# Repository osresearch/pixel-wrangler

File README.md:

# Pixel Wrangler: HDMI to whatever

The Pixel Wrangler is a tool for converting HDMI video into anything else.
It uses an ice40up5k FPGA to decode the video stream and stores a section
of it in the block RAM, which can then be clocked out of the 16 GPIO pins
in any other format required.

Since the FPGA has total flexibility in how it drives the output pins
it is easily adaptable to different protocols.  Some examples that are possible:

* Classic CRT like the original Mac or Hercules monitors
* LED matrices
* Flip dots
* LED strips (ws2812 or other protocols)
* Lots of servos for "wooden mirrors"

## Does it work?

Mostly! The EDID output is good enough to convince Linux to use it as
a normal, if low-resolution, display.  The `mac.bin` monitor mode has
"*live dithering*" to convert the color display into 1-bit, which
works well enough to [play Doom on a 9" Mac Plus](https://www.youtube.com/watch?v=UI3e4YboR_g)!

With `xrandr` it is possible to
have it use a small section of the primary monitor if you don't want a
separate head:

```
xrandr --output HDMI-2 --pos 350x100
```

There are some [problems with the v0 boards](https://github.com/osresearch/pixel-wrangler/issues/22),
one of which reqiures a bodge wire on the i2c lines.  The 5v pullups on
the source side of the HDMI i2c also might cause problems in the FPGA,
so the boards need some redesign.

The [TMDS D1 and D2 channels aren't working](https://github.com/osresearch/pixel-wrangler/issues/23),
so right now only the blue data on channel D0 is used.
This might be a clock phase issue or it might be a larger problem;
more research is needed.

The USB Micro is directly connected to the ice40up5k and the flash
can be loaded with [TinyFPGA bootloader `pixelwrangler` branch](https://github.com/osresearch/TinyFPGA-Bootloader/tree/pixelwrangler)
to allow new bit streams to be uploaded into the device.
The [`multiboot.bin`](image/multiboot.bin) is prebuilt and can
be flashed with your SPI flasher of choice and then the `bootmeta.json`
and `boardmeta.json` can be written into the flash security pages.

## PCB design

[v0 Schematic](pcb/wrangler_v0.pdf) is based on the [UPduino v3.0 by tinyvision.ai](https://www.tindie.com/products/tinyvision_ai/upduino-v31-low-cost-lattice-ice40-fpga-board/),
heavily modified for this specific application.

The HDMI connector has one differential pair carrying a 25 MHz clock and three differential
pairs running at 250 MHz and carrying 10 bits per pixel.  The clock *must* connect
to the one pin on the ice40up5k that has a LVDS connection to the global clock buffer
so that the pixel clock can be quickly fanned-out to the rest of the logic that uses it.
The three data pairs are routed to the LVDS inputs; D0 and D1 are inverted so that they
don't have to cross on the PCB and must be flipped in the logic.

## Limitations

* Only "baseline video" is supported
  * 640x480 @ 60Hz
  * 25 MHz maximum pixel clock
* 1 Mib frame buffer memory in the ice40. Resolutions supported are:
  * 1024x1024x1
  * 512x512x4
  * 256x256x16
  * 256x128x24
* 3.3V IO on GPIO pins
* No protection against shorts or overcurrent. Be careful!
* Boot loader requires button press to reset
* There isn't any USB support in the bit stream tree yet.

## Dithering

Dithering uses Ordered Blue Noise Dithering. Pattern is from [gao-duan](https://github.com/gao-duan/BlueNoise) (MIT Licensed).
Currently limited to a 64x64 size pattern; ideally a larger RGB
image could be loaded from the SPI flash at boot time, which would
allow three channel dithering without repeating across the screen.

## Todo

* [X] Finish board design -- ordered!
* [X] EDID ROM and i2c interface
* [X] DDR on input for ~~high-res~~ inputs
* [X] Classic Mac mode -- working!
* [ ] Fix TMDS channel D1 and D2 decoding
* [ ] Documentation on writing new interfaces
* [ ] LED strip mode
* [ ] Load larger dithering pattern from flash?

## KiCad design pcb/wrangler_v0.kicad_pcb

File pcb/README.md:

This is derived from the UPduino v3 board design by tinyvision-ai-inc:
https://github.com/tinyvision-ai-inc/UPduino-v3.0

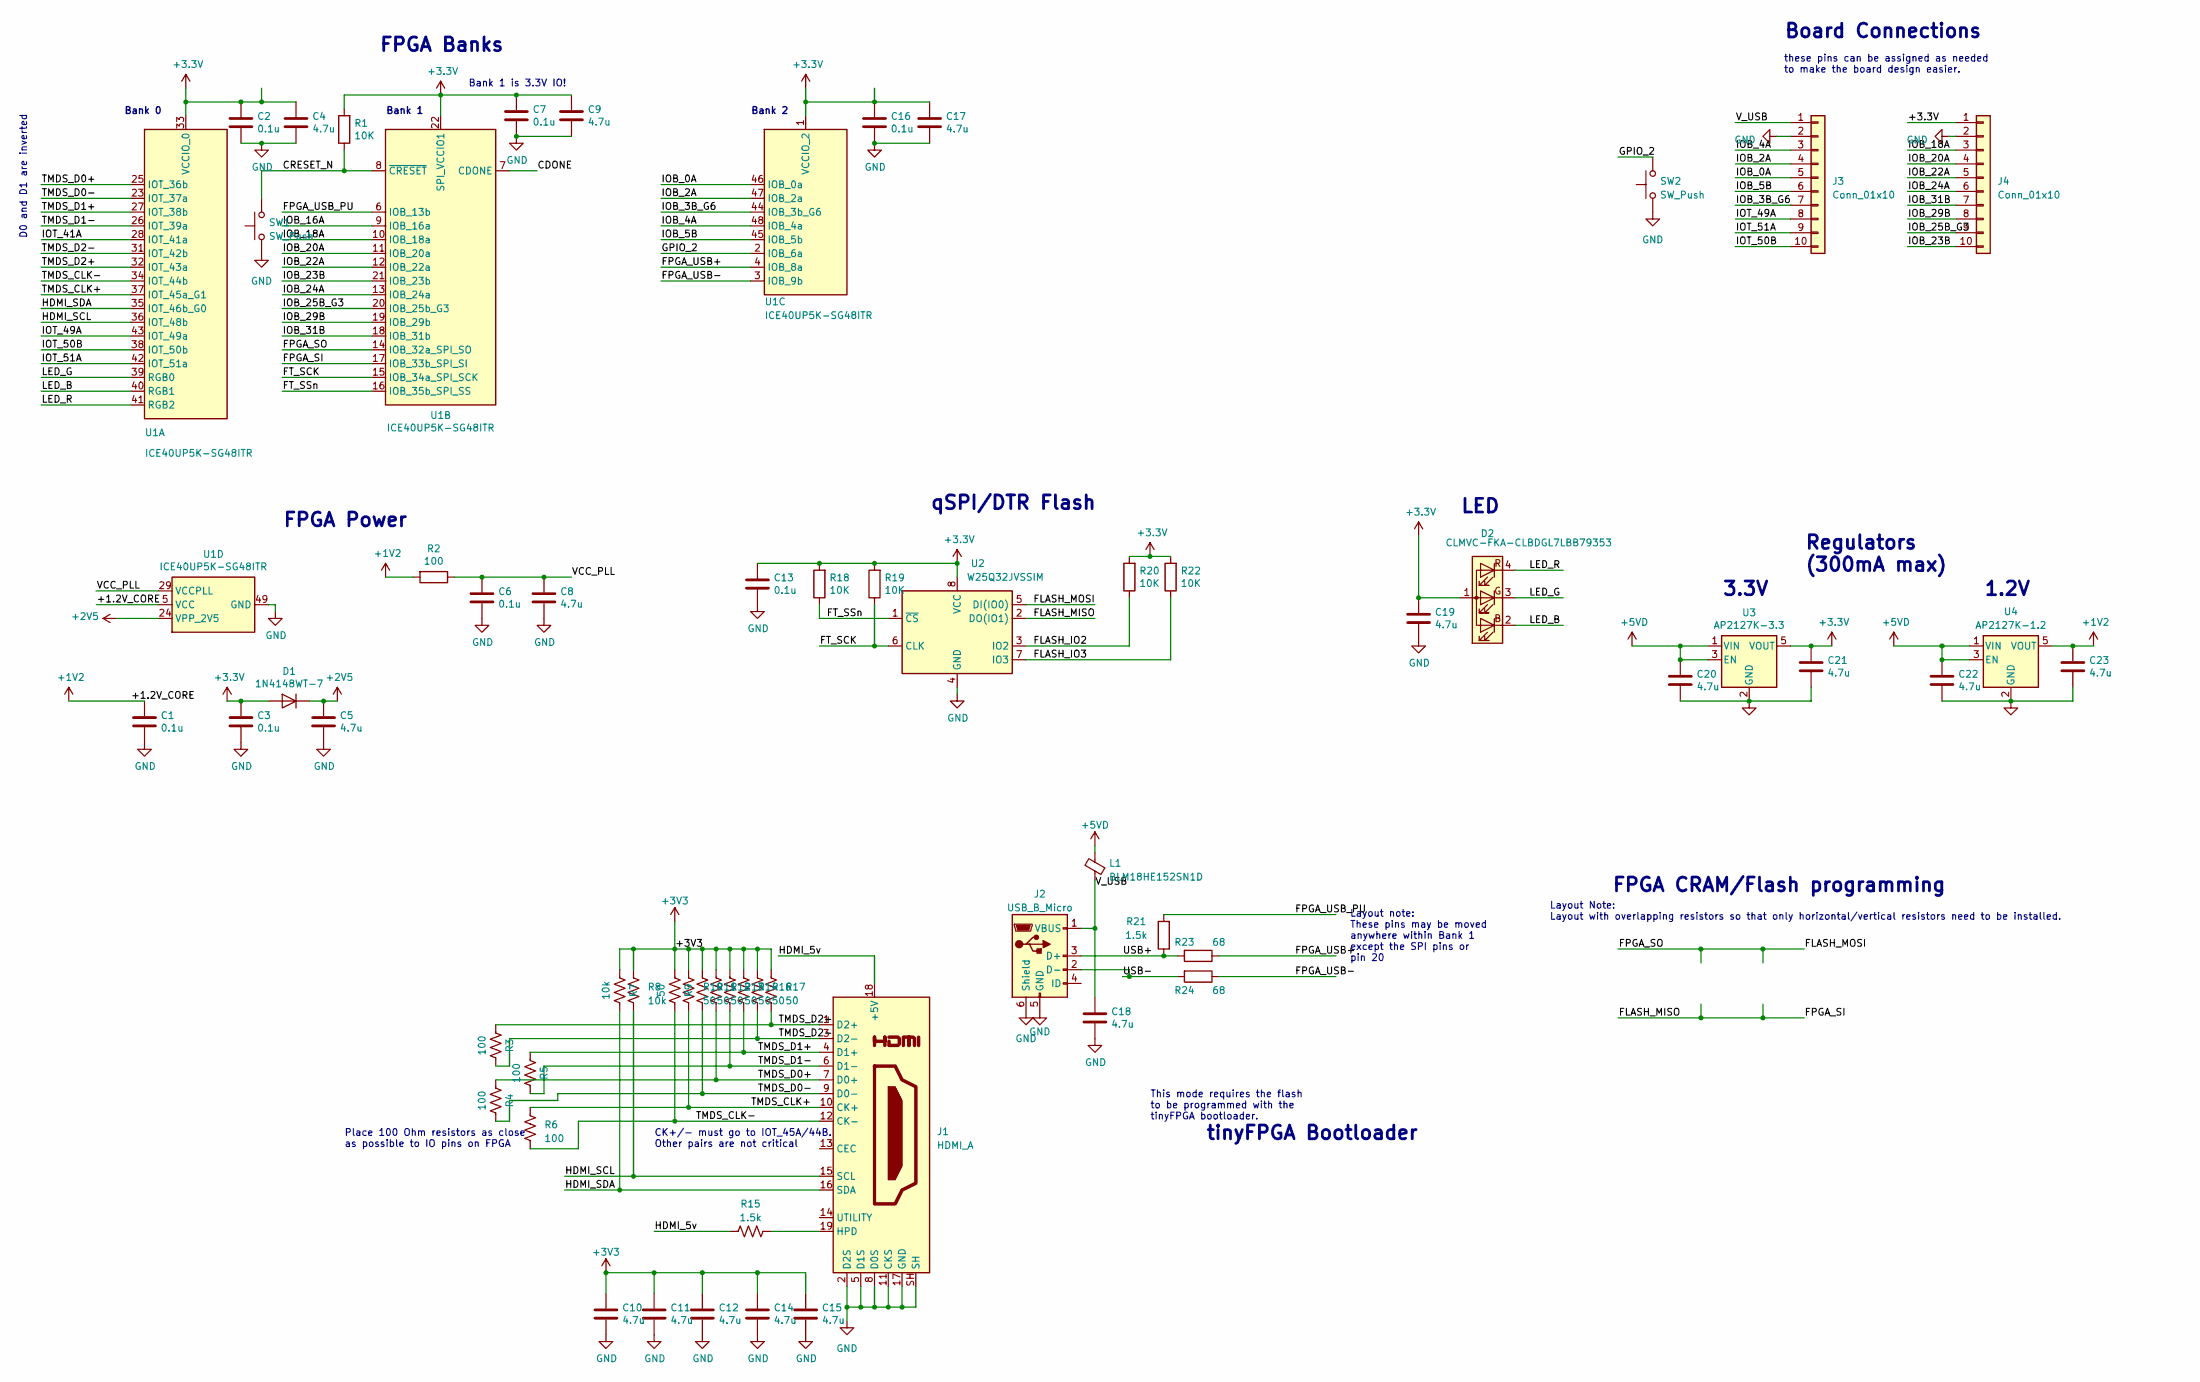
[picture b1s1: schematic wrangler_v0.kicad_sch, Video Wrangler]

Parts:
C1, C3, C6, C7, C13, C16: 0.1u; C_0402_1005Metric
C2: 0.1u; C_0402_1005Metric; MPN C1005X5R0J104K050BA
C4, C5, C8, C9, C10, C11, C12, C14, C15, C17, C18, C19, C20, C21, C22, C23: 4.7u; C_0402_1005Metric
D1: 1N4148WT-7; D_SOD-523
D2: CLMVC-FKA-CLBDGL7LBB79353; LED_Cree-PLCC4_2x2mm_CW
J1: HDMI_A; HDMI_A_Amphenol_10029449-x01xLF_Horizontal
J2: USB_B_Micro; USB_Micro-B_Molex-105017-0001
J3, J4: Conn_01x10; PinHeader_1x10_P2.54mm_Vertical
L1: BLM18HE152SN1D; C_0402_1005Metric
R1, R18, R19, R20, R22: 10K; R_0402_1005Metric
R2, R3, R4, R5, R6: 100; R_0402_1005Metric
R7, R8: 10k; R_0402_1005Metric
R9, R10, R11, R12, R13, R14, R16, R17: 50; R_0402_1005Metric
R15, R21: 1.5k; R_0402_1005Metric
R23, R24: 68; R_0402_1005Metric
SW1, SW2: SW_Push; SW_SPST_CK_KXT3
U1: ICE40UP5K-SG48ITR; QFN-48-1EP_7x7mm_P0.5mm_EP5.6x5.6mm
U2: W25Q32JVSSIM; SOIC-8_5.23x5.23mm_P1.27mm
U3: AP2127K-3.3; SOT-23-5
U4: AP2127K-1.2; SOT-23-5

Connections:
+1V2: C1.1, C23.1, R2.2, U1.5 (VCC), U1.30 (VCC), U4.5 (VOUT)
+2V5: C5.1, D1.1 (K), U1.24 (VPP_2V5)
+5VD: C20.1, C22.1, L1.2, U3.1 (VIN), U3.3 (EN), U4.1 (VIN), U4.3 (EN)
/CDONE: U1.7 (CDONE); also elsewhere on the board
/FLASH_IO2: R20.1, U2.3 (IO2)
/FLASH_IO3: R22.1, U2.7 (IO3)
/FLASH_MISO: U1.17 (IOB_33b_SPI_SI), U2.2 (DO(IO1))
/FLASH_MOSI: U1.14 (IOB_32a_SPI_SO), U2.5 (DI(IO0))
/FPGA_USB+: R23.1, U1.4 (IOB_8a)
/FPGA_USB-: R24.1, U1.3 (IOB_9b)
/FPGA_USB_PU: R21.2, U1.6 (IOB_13b)
/FT_SCK: R19.1, U1.15 (IOB_34a_SPI_SCK), U2.6 (CLK)
/FT_SSn: R18.1, U1.16 (IOB_35b_SPI_SS), U2.1 (~CS)
/HDMI_5v: J1.18 (+5V), R15.1
/HDMI_SCL: J1.15 (SCL), R8.2, U1.36 (IOT_48b)
/HDMI_SDA: J1.16 (SDA), R7.2, U1.35 (IOT_46b_G0)
/IOB_0A: J3.5, U1.46 (IOB_0a)
/IOB_2A: J3.4, U1.47 (IOB_2a)
/IOB_3B_G6: J3.7, U1.44 (IOB_3b_G6)
/IOB_4A: J3.3, U1.48 (IOB_4a)
/IOB_5B: J3.6, U1.45 (IOB_5b)
/IOB_16A: U1.9 (IOB_16a)
/IOB_18A: J4.3, U1.10 (IOB_18a)
/IOB_20A: J4.4, U1.11 (IOB_20a)
/IOB_22A: J4.5, U1.12 (IOB_22a)
/IOB_23B: J4.10, U1.21 (IOB_23b)
/IOB_24A: J4.6, U1.13 (IOB_24a)
/IOB_25B_G3: J4.9, U1.20 (IOB_25b_G3)
/IOB_29B: J4.8, U1.19 (IOB_29b)
/IOB_31B: J4.7, U1.18 (IOB_31b)
/IOT_41A: U1.28 (IOT_41a)
/IOT_49A: J3.8, U1.43 (IOT_49a)
/IOT_50B: J3.10, U1.38 (IOT_50b)
/IOT_51A: J3.9, U1.42 (IOT_51a)
/LED_B: D2.2 (RK), U1.40 (RGB1)
/LED_G: D2.3 (GK), U1.39 (RGB0)
/LED_R: D2.4 (BK), U1.41 (RGB2)
/TMDS_CLK+: J1.10 (CK+), R6.1, R10.2, U1.37 (IOT_45a_G1)
/TMDS_CLK-: J1.12 (CK-), R6.2, R9.2, U1.34 (IOT_44b)
/TMDS_D0+: J1.7 (D0+), R4.1, R12.2, U1.25 (IOT_36b)
/TMDS_D0-: J1.9 (D0-), R4.2, R11.2, U1.23 (IOT_37a)
/TMDS_D1+: J1.4 (D1+), R5.1, R14.2, U1.27 (IOT_38b)
/TMDS_D1-: J1.6 (D1-), R5.2, R13.2, U1.26 (IOT_39a)
/TMDS_D2+: J1.1 (D2+), R3.1, R17.2, U1.32 (IOT_43a)
/TMDS_D2-: J1.3 (D2-), R3.2, R16.2, U1.31 (IOT_42b)
/USB+: J2.3 (D+), R21.1, R23.2
/USB-: J2.2 (D-), R24.2
/VCC_PLL: C6.1, C8.1, R2.1, U1.29 (VCCPLL)
/V_USB: C18.1, J2.1 (VBUS), J3.1, L1.1
GND: C1.2, C2.2, C3.2, C4.2, C5.2, C6.2, C7.2, C8.2, C9.2, C10.2, C11.2, C12.2, C13.2, C14.2, C15.2, C16.2, C17.2, C18.2, C19.2, C20.2, C21.2, C22.2, C23.2, J1.2 (D2S), J1.5 (D1S), J1.8 (D0S), J1.11 (CKS), J1.17 (GND), J1.SH, J2.5 (GND), J2.6 (Shield), J3.2, J4.2, SW1.1, SW2.1, U1.49 (GND), U2.4 (GND), U3.2 (GND), U4.2 (GND); also elsewhere on the board
unnamed: J1.19 (HPD), R15.2

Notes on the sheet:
Bank 1
Bank 1 is 3.3V IO!
Layout note: These pins may be moved anywhere within Bank 1 except the SPI pins or pin 20
tinyFPGA Bootloader
LED
FPGA Power
This mode requires the flash to be programmed with the tinyFPGA bootloader.
CK+/- must go to IOT_45A/44B. Other pairs are not critical
Layout Note: Layout with overlapping resistors so that only horizontal/vertical resistors need to be installed.
3.3V
D0 and D1 are inverted
Place 100 Ohm resistors as close as possible to IO pins on FPGA
Bank 0
Board Connections
1.2V
Bank 2
qSPI/DTR Flash
FPGA Banks
Regulators (300mA max)
these pins can be assigned as needed to make the board design easier.
FPGA CRAM/Flash programming

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
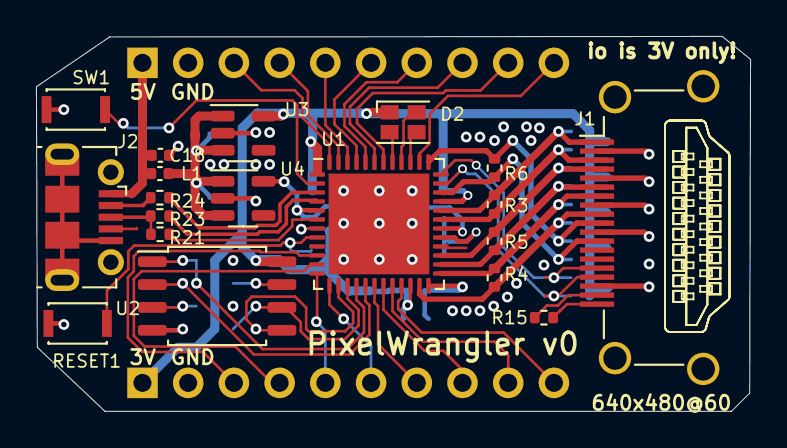
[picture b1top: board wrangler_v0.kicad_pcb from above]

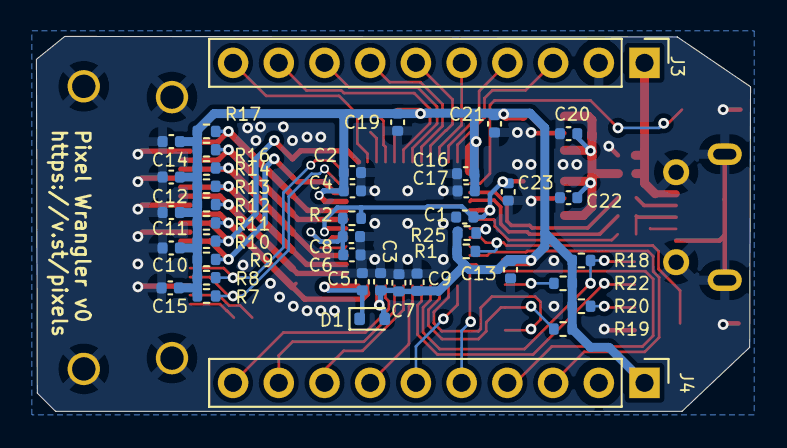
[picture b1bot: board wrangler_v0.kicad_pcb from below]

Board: 4 copper layers, 39.7 x 20.8 mm, 61 parts (42 on the bottom side), 52 nets.

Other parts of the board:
R25: 2.2k; R_0402_1005Metric
RESET1: SW_Push; SW_SPST_CK_KXT3

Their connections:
/CDONE: R25.1; also elsewhere on the board
GND: RESET1.1; also elsewhere on the board

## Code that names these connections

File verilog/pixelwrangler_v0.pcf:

# The LED pins are using the current controlled outputs
# and are negative logic (write a 0 to turn on).
set_io -nowarn led_r	41
set_io -nowarn led_g	39
set_io -nowarn led_b	40

set_io -nowarn spi_cs 16 # Drive high to ensure that the SPI flash is disabled
set_io -nowarn spi_sck 15
set_io -nowarn spi_mosi 14
set_io -nowarn spi_msio 17

set_io -nowarn pin_usbp 4 # IOB_8A
set_io -nowarn pin_usbn 3 # IOB_9B
set_io -nowarn pin_usb_pu 6 # IOB_13B

set_io -nowarn sw1 2 # IOB_6A

# HDMI input
set_io -nowarn tmds_d0p 25 # IOT_36B; needs inversion
set_io -nowarn tmds_d0n 23 # IOT_37A
set_io -nowarn tmds_d1p 27 # IOT_38B; needs inversion
set_io -nowarn tmds_d1n 26 # IOT_39A
set_io -nowarn tmds_d2p 32 # IOT_43A
set_io -nowarn tmds_d2n 31 # IOT_42B
set_io -nowarn tmds_clkp 37 # IOT_45A_G1
set_io -nowarn tmds_clkn 34 # IOT_44b
set_io -nowarn hdmi_sda 35 # IOT_46B_G0
set_io -nowarn hdmi_scl 36 # IOT_48b

# GPIO bank 0, bottom side
set_io -nowarn gpio_0_0 10 # IOB_18A
set_io -nowarn gpio_0_1 11 # IOB_20A
set_io -nowarn gpio_0_2 12 # IOB_22A
set_io -nowarn gpio_0_3 13 # IOB_24A
set_io -nowarn gpio_0_4 18 # IOB_31B
set_io -nowarn gpio_0_5 19 # IOB_29B
set_io -nowarn gpio_0_6 20 # IOB_25B_G
set_io -nowarn gpio_0_7 21 # IOB_23B

# GPIO bank 1, top side
set_io -nowarn gpio_1_0 48 # IOB_4A
set_io -nowarn gpio_1_1 47 # IOB_2A
set_io -nowarn gpio_1_2 46 # IOB_0A
set_io -nowarn gpio_1_3 45 # IOB_5B
set_io -nowarn gpio_1_4 44 # IOB_3B_G6
set_io -nowarn gpio_1_5 43 # IOB_49A
set_io -nowarn gpio_1_6 42 # IOB_51A
set_io -nowarn gpio_1_7 38 # IOB_50B

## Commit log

2023-02-16 import of train display code
2023-02-16 forked project from train display
2023-02-17 pixel wrangler v0 board (based on upduino v3 and heavily modified)
2023-02-17 updated with comments from revspace and matt
2023-02-17 PCB and upduino link
2023-02-17 forgot the uart
2023-02-17 ignore generated files
2023-02-18 ignore gerber files
2023-02-18 more auto generated files
2023-02-18 pcb: added CDONE pullup resistor and some silkscreen tweaks
2023-02-18 README: more todo
2023-02-18 jlpcb export parameters
2023-02-18 updated pdf and images for v0
2023-02-18 ignore vi temp files
2023-02-18 move all tmds stuff into tmds.v
2023-02-18 split serdes into hdmi and tmds, ported train display code over, vsync is gliching sometimes
2023-02-18 enable DDR mode for the PLL
2023-02-18 re-enable the other channels
2023-02-18 slow down the LED matrix scanning a bit, it was causing static on the display
2023-02-19 ddr phase only requires 3 bits and counts up to 5 (#16)
2023-02-19 640x480 EDID, untested
2023-02-20 i2c almost works?
2023-02-20 uart tx/rx with baud clock generator
2023-02-20 load the edid data and instantiate an i2c device
2023-02-20 edid: better 640x480? (#3)
2023-02-20 i2c: fix block read mode address pre-increment (#17)
2023-02-20 rename clk to hdmi_clk in several places
2023-02-20 hdmi_reset: reset the state of the tmds decoder if no valid sync signals are received (#18)
2023-02-21 move pwm into separate file, use the SB_RGBA_DRV to avoid overcurrent
2023-02-21 split top module out so that the displays can be more modular
2023-02-23 rgb: silence a warning about enable size
2023-02-23 classic mac mode draws a apple logo on a mac plus!
2023-02-24 pwm: fix rgb assignment for the upduino (maybe wrong for pixelwrangler boards)
2023-02-24 vsync glitches: debug by waiting for two clocks
2023-02-24 dithered mac display looks better! occasional glitches and off-by-one error on first pixels, but almost there
2023-02-24 mac: fixed some off-by-one errors, increased dither size to 64, and it looks good!
2023-02-25 working multiboot image for the pixel wrangler v0 board
2023-02-26 dither: fix LUT ram for noise pattern
2023-02-26 tmds: add INVERT option for differential pairs that are flipped
2023-02-26 top: use pixelwrangler pins (untested)
2023-02-26 ignore vi tmp files
2023-02-26 relocate multiboot.bin
2023-02-26 tinyprog boardmeta and programming tools
2023-02-27 Makefile: remove duplicate (and bad) icepack
2023-02-27 hdmi_sda: temporarily bodge to gpio_1_7
2023-02-27 dither: temporarily use only blue
2023-02-27 tmds: split clk/pll setup into separate module
2023-02-27 hack around issue in gpio 35 for hdmi_sda
2023-02-27 move div3 and spram and others into util
2023-02-28 macplus update
2023-02-28 tristate: add pullup optoin
2023-02-28 dither: larger noise matrices (does not fit yet)
2023-02-28 tmds: replace block ram with just two flip flop stages
2023-02-28 top: rename sw1, enable pullups on it, allow user to reset hdmi, expose bit clock to user
2023-02-28 more images for readme
2023-02-28 image fixups
2023-02-28 bootloader docs
2023-02-28 mac: off by one on the window size? this seems wrong
2023-03-01 fix tmds d1 and d2 channels, use them in the dithered output
2023-03-04 Makefile: use clock constraints
2023-03-04 mac: debug hdmi vsync on gpio
2023-03-04 allow user code to define tx/rx pins
2023-03-04 use dpram in 2-bit write, 16-bit read for clock crossing
    This overhauls the TMDS decoder and clock crossing from the
    bit_clk domain to hdmi_clk domain by using a dpram block
    in 2-bit write, 16-bit read to act as a clock crossing and
    shift-register.
    Timing analysis is 133 MHz, which should be in excess of
    the 125MHz required for the bit clock, but this requires
2023-03-04 pll: add fixed delay and suddenly all the channels look good
2023-03-08 Makefile: --timing-allow-fail and allow 120 MHz
2023-03-08 dither: triangle test for diagnosing which channels are glitchy
2023-03-08 lots of things to try to track down the glitches
2023-03-22 create a gamma table
2023-03-22 print the tmds patterns
2023-03-22 invert the raw pins
2023-03-22 enforce 125 mhz bit clock, 25 mhz hdmi clock
2023-03-22 ignore .hex files
2023-03-22 Makefile: create gamma files, rename prog target
2023-03-22 hub75 led matrix protocol with gamma mapping
2023-03-22 absurd number of hacks that really need to be cleaned up but committed so that we do not lose them
